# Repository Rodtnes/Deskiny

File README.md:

# Deskiny
/ˈdes.kɪ.n-i/
A tiny project one year in the making. A 42 key split wireless keyboard powered by zmk running on two seeeduino xiao boards. Inspired by the TOTEM by GEIGEIGEIST, Deskiny is an attempt to create a layout which functions with a full alpha layer for nordic layouts (æøå) while retaining a compact form factor.

## Gallery

## Case (WIP)
The case  can be found [here](https://a360.co/4eJjC5Y) as a fusion 360 file.
The case is designed to be 3D printed in two parts and then glued together, there is enough space in the case to add foam underneath the board for a bit of sound dampning. *Please note that PCB was designed with holes for M2 screws to be use to secure the PCB to the case, which is not yet implemented.* The case is also designed to be use with just a switch i had lying around so feel free to modify the case to fit your switch of choice.

## Partlist
The following parts are required for the build
- 2x Seeeduino Xiao nrf58
- 2x pcb's
- 2x 3D printed cases
- 42x kailh v1 lowprofile switches
- 42x 1N4148W diodes THT or SMD (SOD 123)
- 2x Li-Pol-battery 3,7V 402050
- Wire for the power switch and battery
- Plastic glue

The following parts are optional
- 42x kailh v1 hotswap sockets
- 6x neodynium magnets 10x10x5mm*
- 2x power switch
*\*The case is big enough to accomodate a variety of different magnet sizes these are just the ones I chose.

## Assembly (WIP)
This is only a rough outline of assembly, if there is interest i wil make a proper build guide.

1. Solder the diodes to the pcb (make sure to solder them in the correct orientation)
2. (optional) Solder hotswap sockets to the pcb
3. Solder microcontroller to the pcb to the top side of the pcb, you can use diode legs to align the microcontroller.
4. Solder the battery connection on the bottom side of the pcb to the microcontroller
5. Solder the jumpers on the bottom side of the pcb
6. Solder connections to the (optional) power switch and battery
7. (optional) glue 3 magnets in each half of the case (positioned in the upper left and right coners and bottom middle)
8. Slide the pcb into the case and push the switches into the pcb and case combo
9. (optional) solder the switches to the pcb
10. (optional) glue in the power switch
11. glue the battery into the case
12. glue in the bottom of the case

## Firmware
The zmk firmware can be found [here](zmk-config-Deskiny) keymaps can esily be created online using the elephant 42 board [here](https://nickcoutsos.github.io/keymap-editor/)

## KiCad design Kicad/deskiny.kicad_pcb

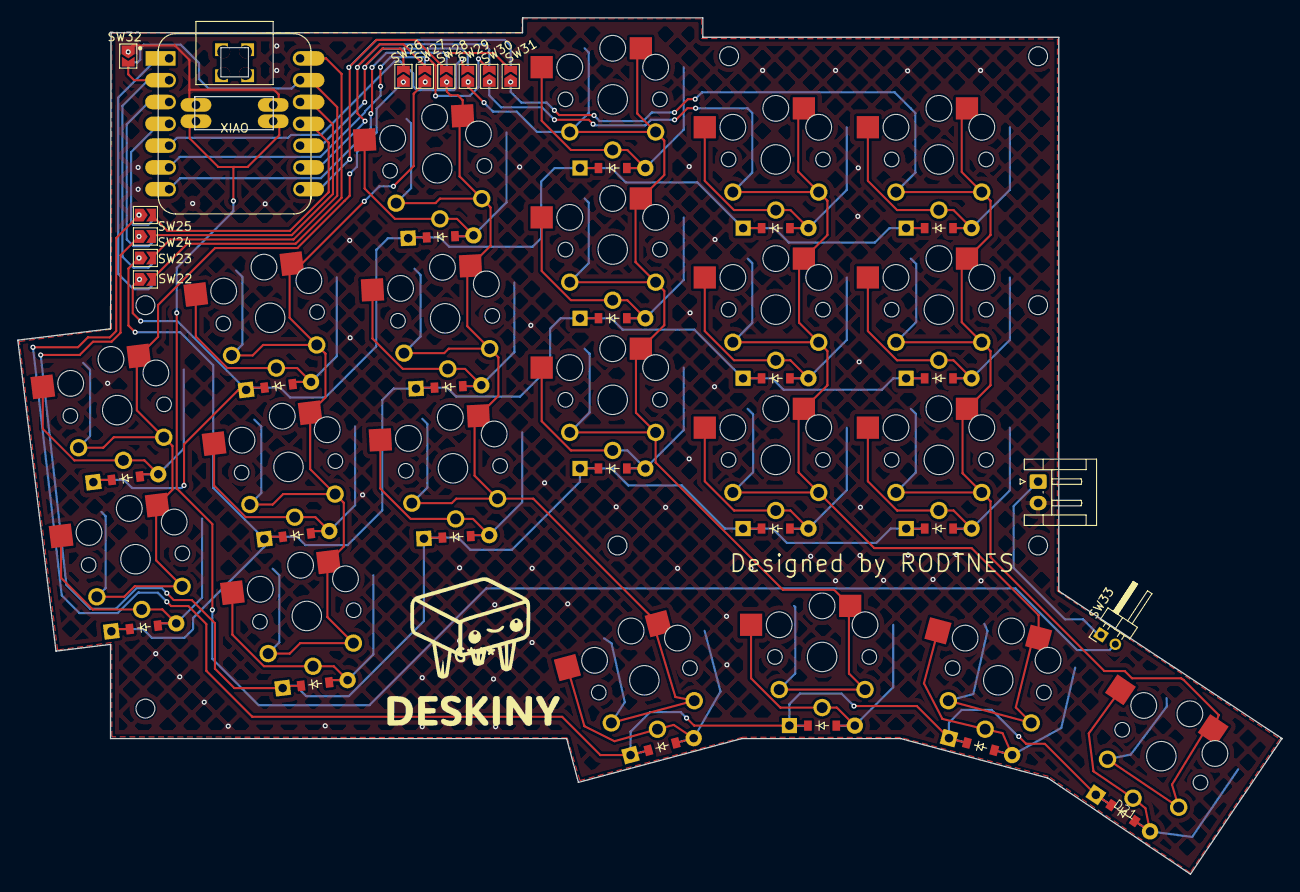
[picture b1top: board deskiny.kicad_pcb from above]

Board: 2 copper layers, 147.3 x 99.8 mm, 56 parts (0 on the bottom side), 48 nets.

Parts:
BT1: Battery_Cell; JST_EH_S2B-EH_1x02_P2.50mm_Horizontal
D1, D2, D3, D4, D5, D6, D7, D8, D9, D10, D11, D12, D13, D14, D15, D16, D17, D18, D19, D20, D21: 1N4448; Diode
SW1, SW2, SW3, SW4, SW5, SW6, SW7, SW8, SW9, SW10, SW11, SW12, SW13, SW14, SW15, SW16, SW17, SW18, SW19, SW20, SW21: SW_Push_45deg; Key
SW22, SW23, SW24, SW25, SW26, SW27, SW28, SW29, SW30, SW31, SW32: SW_SPDT_312; SolderJumper
SW33: SW_DIP_x01; PinHeader_1x02_P2.00mm_Horizontal
U1: xiao-ble; KeyboardXIAO

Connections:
5V Left: SW22.3 (A), U1.1 (A2/0.02_H)
5V Right: SW22.2 (C), U1.14 (5V)
BAT: SW33.2, U1.19 (BAT)
Col 0: SW1.1, SW2.1, SW26.1 (B)
Col 0 Left: SW26.2 (C), SW29.3 (A), U1.10 (A5_MISO/1.14)
Col 0 Right: SW26.3 (A), SW29.2 (C), U1.5 (A8_SDA/0.04_H)
Col 1: SW3.1, SW4.1, SW5.1, SW27.1 (B)
Col 1 Left: SW27.2 (C), SW30.3 (A), U1.9 (A7_SCK/1.13)
Col 1 Right: SW27.3 (A), SW30.2 (C), U1.6 (A9_SCL/0.05_H)
Col 2: SW6.1, SW7.1, SW8.1, SW9.1, SW28.1 (B)
Col 2 Left: SW28.2 (C), SW31.3 (A), U1.8 (B9_RX/1.12)
Col 2 Right: SW28.3 (A), SW31.2 (C), U1.7 (B8_TX/1.11)
Col 3: SW10.1, SW11.1, SW12.1, SW13.1, SW29.1 (B)
Col 4: SW14.1, SW15.1, SW16.1, SW17.1, SW30.1 (B)
Col 5: SW18.1, SW19.1, SW20.1, SW21.1, SW31.1 (B)
GND: BT1.2 (-), SW32.1 (B), U1.20 (GND)
GND Left: SW23.3 (A), SW32.2 (C), U1.2 (A4/0.03_H)
GND Right: SW23.2 (C), SW32.3 (A), U1.13 (GND)
unnamed: BT1.1 (+), SW33.1
unnamed: D1.2 (A), SW1.2
unnamed: D2.2 (A), SW2.2
unnamed: D3.2 (A), SW3.2
unnamed: D4.2 (A), SW4.2
unnamed: D5.2 (A), SW5.2
unnamed: D6.2 (A), SW6.2
unnamed: D7.2 (A), SW7.2
unnamed: D8.2 (A), SW8.2
unnamed: D9.2 (A), SW9.2
unnamed: D10.2 (A), SW10.2
unnamed: D11.2 (A), SW11.2
unnamed: D12.2 (A), SW12.2
unnamed: D13.2 (A), SW13.2
unnamed: D14.2 (A), SW14.2
unnamed: D15.2 (A), SW15.2
unnamed: D16.2 (A), SW16.2
unnamed: D17.2 (A), SW17.2
unnamed: D18.2 (A), SW18.2
unnamed: D19.2 (A), SW19.2
unnamed: D20.2 (A), SW20.2
unnamed: D21.2 (A), SW21.2
Row 0: D1.1 (K), D3.1 (K), D6.1 (K), D10.1 (K), D14.1 (K), D18.1 (K), SW22.1 (B)
Row 1: D2.1 (K), D4.1 (K), D7.1 (K), D11.1 (K), D15.1 (K), D19.1 (K), SW23.1 (B)
Row 2: D5.1 (K), D8.1 (K), D12.1 (K), D16.1 (K), D20.1 (K), SW24.1 (B)
Row 2 Left: SW24.2 (C), U1.12 (3V3)
Row 2 Right: SW24.3 (A), U1.3 (A10/0.28)
Row 3: D9.1 (K), D13.1 (K), D17.1 (K), D21.1 (K), SW25.1 (B)
Row 3 Left: SW25.2 (C), U1.11 (A6_MOSI/1.15)
Row 3 Right: SW25.3 (A), U1.4 (A11/0.29)
